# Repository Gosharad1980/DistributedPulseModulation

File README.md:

# DistributedPulseModulation

Distributed pulse modulation done like with the old P82C150, but with descrete components

## Theory of operation

With a regular Pulse Width Modulation (PWM), all the pulses are grouped in a same and unique pulse over the whole period.
On Distributed Pulse Modulation (DPM) and Dyadic Descrete Pulse Modulation (DDPM), the aim is to distribute all the "sub-pulses" throughout the whole period.

## Two advantages :
* spectrum with more high frequencies than PWM : easier filtering in case of A/D conversion
* as the pulse distribution is continuously evaluated : a threshold modification, before the period end, is taken into account without delay

### Old P82C150 for DPM implementation
[P82C150 - Application note](https://www.nxp.com/docs/en/application-note/AN94088.pdf)

[P82C150 datasheet](https://www.digchip.com/datasheets/parts/datasheet/364/P82C150AHT-pdf.php)

### DDPM implementation based on Paolo S. Crovetti thesis
[Thèse : Paolo S. Crovetti](https://www.researchgate.net/publication/309012492_All-Digital_High_Resolution_DA_Conversion_by_Dyadic_Digital_Pulse_Modulation)

## The breakout board

###  Features
	PWM (Pulse Width Modulation)
	DPM P82C150-like (Distributed Pulse Modulation)
	DDPM (Dyadic Discrete Pulse Modulation)

### MCP23017 Port A & B

	MCP23017 is an I2C 16bits IO expander
	Port A & B are used to control the board
	Prescaler decoding values :
	0x00	1
	0x01	2
	0x02	8
	0x03	16
	0x04	64
	0x05	256
	0x06	1024
	0x07	4096

## Choose your feature and do not populate the useless chips

### PWM

* do not populate the CD74HCT4053
* place the jumpers as describe in the silkscreen schematic (PWM)

### DPM

* do not populate the CD74HCT4053
* place the jumpers as describe in the silkscreen schematic (DPM/DDPM)

### DDPM

* do not populate the 74LS85
* place the jumpers as describe in the silkscreen schematic (DPM/DDPM)

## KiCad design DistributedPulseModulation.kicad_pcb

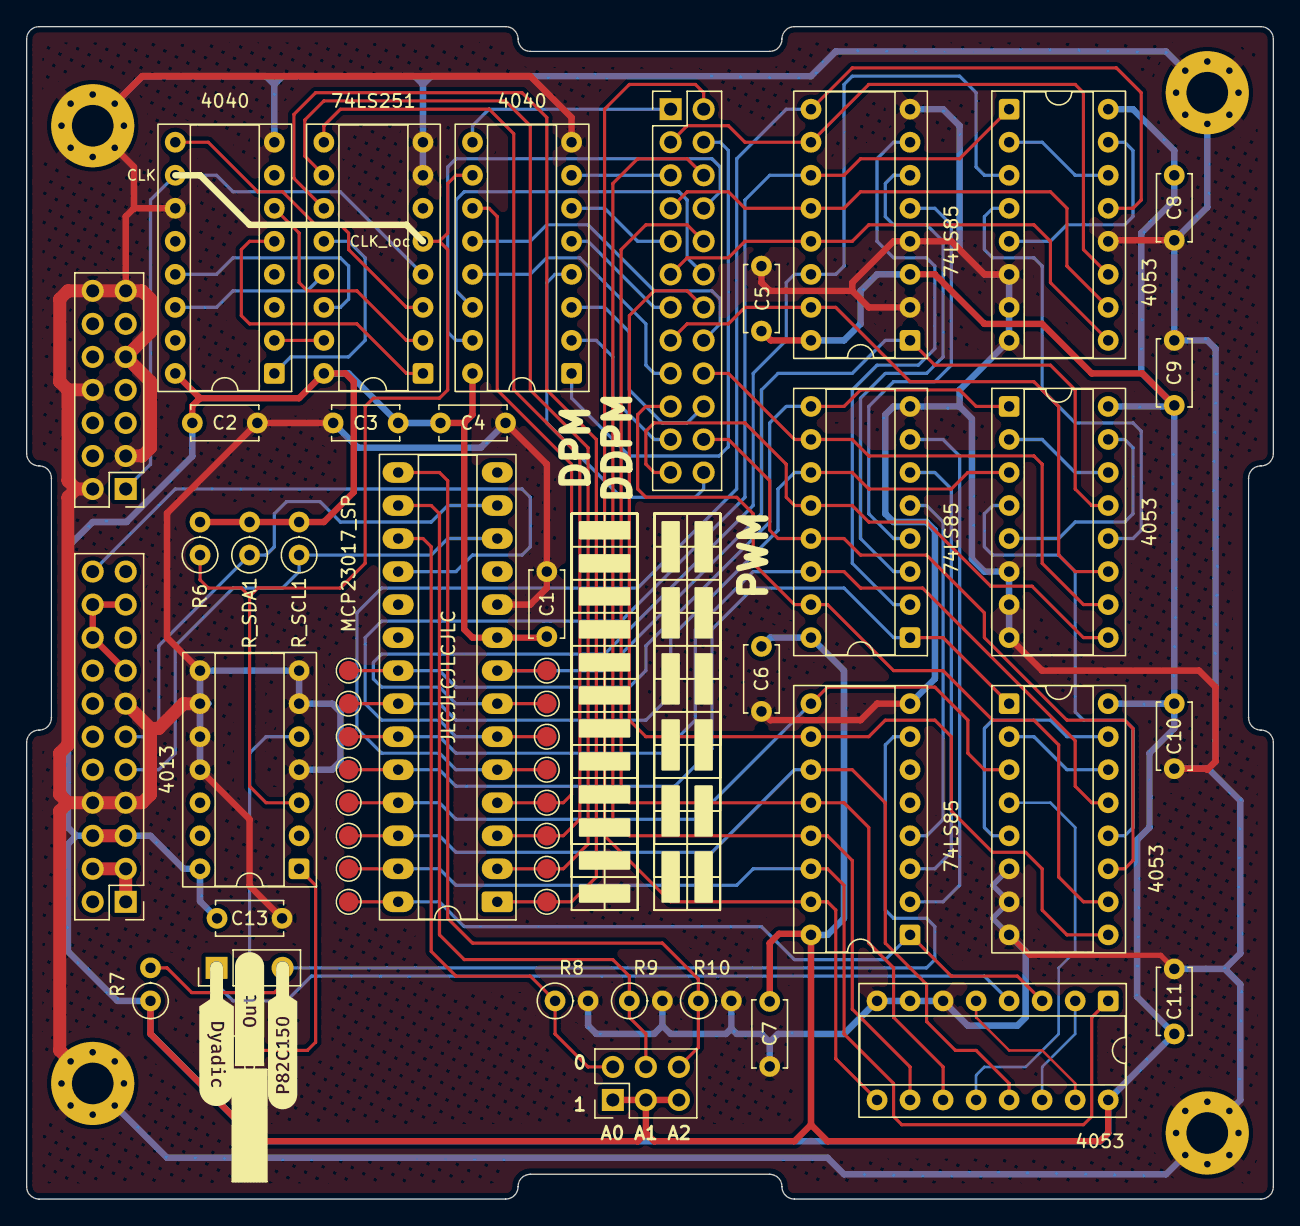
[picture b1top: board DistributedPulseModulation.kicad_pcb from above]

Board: 2 copper layers, 95.9 x 90.2 mm, 61 parts (1 on the bottom side), 80 nets.

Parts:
C1, C2, C3, C4, C5, C6, C7, C8, C9, C10, C11, C13: 0.1µF; C_Disc_D5.0mm_W2.5mm_P5.00mm
H1, H2, H3, H4: MountingHole_Pad; MountingHole_3.2mm_M3_Pad_Via
J1: Conn_02x12_Odd_Even; PinHeader_2x12_P2.54mm_Vertical
J2: Conn_01x01; PinSocket_1x01_P2.54mm_Horizontal
J3: Conn_02x03_Odd_Even; PinHeader_2x03_P2.54mm_Vertical
JP5: Jumper_3_Open; PinHeader_1x03_P2.54mm_Vertical
PCIe_CAN_1: Conn_02x07_Odd_Even; PinHeader_2x07_P2.54mm_Vertical
PCIe_SPI_1: Conn_02x11_Odd_Even; PinHeader_2x11_P2.54mm_Vertical
R6, R7, R8, R9, R10: 2.2K; R_Axial_DIN0207_L6.3mm_D2.5mm_P2.54mm_Vertical
R_SCL1: 4.7 kOhm; R_Axial_DIN0207_L6.3mm_D2.5mm_P2.54mm_Vertical
R_SDA1: 4.7 kOhm; R_Axial_DIN0207_L6.3mm_D2.5mm_P2.54mm_Vertical
TP_A0, TP_A1, TP_A2, TP_A3, TP_A4, TP_A5, TP_A6, TP_A7, TP_A8, TP_A9, TP_A10, TP_A11: TestPoint_Probe; TestPoint_Pad_D1.5mm
TP_PS0, TP_PS1, TP_PS2: TestPoint_Probe; TestPoint_Pad_D1.5mm
TP_~{CntEN}0: TestPoint_Probe; TestPoint_Pad_D1.5mm
U1: 74LS251; DIP-16_W7.62mm_Socket
U2: 4013; DIP-14_W7.62mm_Socket
U4: MCP23017_SP; DIP-28_W7.62mm_Socket_LongPads
U7, U10, U11, U12: 4053; DIP-16_W7.62mm_Socket
U8, U9: 4040; DIP-16_W7.62mm_Socket
U25, U28, U31: 74LS85; DIP-16_W7.62mm_Socket
kibuzzard-6ADD3B59: G***; kibuzzard-6ADD3B59
kibuzzard-68110D32: G***; kibuzzard-68110D32
kibuzzard-6811091F: G***; kibuzzard-6811091F
kibuzzard-68110930: G***; kibuzzard-68110930

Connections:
+5V: C1.2, C2.2, C3.2, C4.2, C5.2, C6.2, C7.2, C8.2, C9.2, C10.2, C11.2, C13.2, J3.1, J3.3, J3.5, PCIe_SPI_1.5, PCIe_SPI_1.6, R6.2, R7.1, R_SCL1.2, R_SDA1.2, U1.16 (VCC), U2.14 (VDD), U4.9 (VDD), U7.16 (VDD), U8.16 (VDD), U9.16 (VDD), U10.16 (VDD), U11.16 (VDD), U12.16 (VDD), U25.3 (Ia=b), U25.16 (VCC), U28.16 (VCC), U31.16 (VCC)
/A0: TP_A0.1 (1_1), U4.5 (GPB4), U7.13 (X1), U25.9 (B0)
/A1: TP_A1.1 (1_1), U4.6 (GPB5), U7.1 (Y1), U25.11 (B1)
/A2: TP_A2.1 (1_1), U4.7 (GPB6), U7.3 (Z1), U25.14 (B2)
/A3: TP_A3.1 (1_1), U4.8 (GPB7), U10.13 (X1), U25.1 (B3)
/A4: TP_A4.1 (1_1), U4.21 (GPA0), U10.1 (Y1), U28.9 (B0)
/A5: TP_A5.1 (1_1), U4.22 (GPA1), U10.3 (Z1), U28.11 (B1)
/A6: TP_A6.1 (1_1), U4.23 (GPA2), U11.13 (X1), U28.14 (B2)
/A7: TP_A7.1 (1_1), U4.24 (GPA3), U11.1 (Y1), U28.1 (B3)
/A8: TP_A8.1 (1_1), U4.25 (GPA4), U11.3 (Z1), U31.9 (B0)
/A9: TP_A9.1 (1_1), U4.26 (GPA5), U12.13 (X1), U31.11 (B1)
/A10: TP_A10.1 (1_1), U4.27 (GPA6), U12.1 (Y1), U31.14 (B2)
/A11: TP_A11.1 (1_1), U4.28 (GPA7), U12.3 (Z1), U31.1 (B3)
/ADR0: J3.2, R8.1, U4.17 (A2)
/ADR1: J3.4, R9.1, U4.16 (A1)
/ADR2: J3.6, R10.1, U4.15 (A0)
/Bus de fond panier/+3.3V: PCIe_SPI_1.15, PCIe_SPI_1.18, PCIe_SPI_1.19, PCIe_SPI_1.20
/Bus de fond panier/+Batt: PCIe_SPI_1.1, PCIe_SPI_1.3, PCIe_SPI_1.4
/CNT_A0: J1.2, U12.9 (C), U31.15 (A3)
/CNT_A1: J1.6, U12.10 (B), U31.13 (A2)
/CNT_A2: J1.10, U12.11 (A), U31.12 (A1)
/CNT_A3: J1.14, U11.9 (C), U31.10 (A0)
/CNT_A4: J1.19, U11.10 (B), U28.15 (A3)
/CNT_A5: J1.22, U11.11 (A), U28.13 (A2)
/CNT_A6: J1.23, U10.9 (C), U28.12 (A1)
/CNT_A7: J1.18, U10.10 (B), U28.10 (A0)
/CNT_A8: J1.15, U10.11 (A), U25.15 (A3)
/CNT_A9: J1.11, U7.9 (C), U25.13 (A2)
/CNT_A10: J1.7, U7.10 (B), U25.12 (A1)
/CNT_A11: J1.3, U7.11 (A), U25.10 (A0)
/Clock_loc: R6.1, U1.5 (Y), U2.3 (C), U8.10 (CLK)
/Div_2: U1.3 (I1), U9.9 (Q0)
/Div_8: U1.2 (I2), U9.6 (Q2)
/Div_16: U1.1 (I3), U9.5 (Q3)
/Div_64: U1.15 (I4), U9.2 (Q5)
/Div_256: U1.14 (I5), U9.13 (Q7)
/Div_1024: U1.13 (I6), U9.14 (Q9)
/Div_4096: U1.12 (I7), U9.1 (Q11)
/Q0: J1.1, U8.9 (Q0)
/Q1: J1.5, U8.7 (Q1)
/Q2: J1.9, U8.6 (Q2)
/Q3: J1.13, U8.5 (Q3)
/Q4: J1.20, U8.3 (Q4)
/Q5: J1.21, U8.2 (Q5)
/Q6: J1.24, U8.4 (Q6)
/Q7: J1.17, U8.13 (Q7)
/Q8: J1.16, U8.12 (Q8)
/Q9: J1.12, U8.14 (Q9)
/Q10: J1.8, U8.15 (Q10)
/Q11: J1.4, U8.1 (Q11)
Clock: PCIe_CAN_1.1, U1.4 (I0), U9.10 (CLK)
DDPM: JP5.1 (A), U12.4 (Z)
DPM: J2.1 (Pin_1_1), U2.1 (Q)
DPM_PWM: JP5.3 (B), R7.2, U31.7 (Oa<b)
Ground: C1.1, C2.1, C3.1, C4.1, C5.1, C6.1, C7.1, C8.1, C9.1, C10.1, C11.1, C13.1, H1.1 (1_1), H2.1 (1_1), H3.1 (1_1), H4.1 (1_1), PCIe_CAN_1.2, PCIe_CAN_1.3, PCIe_CAN_1.8, PCIe_CAN_1.9, PCIe_CAN_1.13, PCIe_CAN_1.14, PCIe_SPI_1.7, PCIe_SPI_1.8, PCIe_SPI_1.13, R8.2, R9.2, R10.2, U1.7 (~OE), U1.8 (GND), U2.4 (R), U2.6 (S), U2.7 (VSS), U2.8 (S), U2.9 (D), U2.10 (R), U2.11 (C), U4.10 (VSS), U7.6 (Inh), U7.7 (VEE), U7.8 (VSS), U7.12 (X0), U8.8 (VSS), U9.8 (VSS), U9.11 (Reset), U10.6 (Inh), U10.7 (VEE), U10.8 (VSS), U11.6 (Inh), U11.7 (VEE), U11.8 (VSS), U12.6 (Inh), U12.7 (VEE), U12.8 (VSS), U25.2 (Ia<b), U25.4 (Ia>b), U25.8 (GND), U28.8 (GND), U31.8 (GND)
unnamed: JP5.2 (C), U2.5 (D)
unnamed: U7.2 (Y0), U7.14 (X)
unnamed: U7.5 (Z0), U7.15 (Y)
unnamed: U7.4 (Z), U10.12 (X0)
unnamed: U10.2 (Y0), U10.14 (X)
unnamed: U10.5 (Z0), U10.15 (Y)
unnamed: U10.4 (Z), U11.12 (X0)
unnamed: U11.2 (Y0), U11.14 (X)
unnamed: U11.5 (Z0), U11.15 (Y)
unnamed: U11.4 (Z), U12.12 (X0)
unnamed: U12.2 (Y0), U12.14 (X)
unnamed: U12.5 (Z0), U12.15 (Y)
unnamed: U25.7 (Oa<b), U28.2 (Ia<b)
unnamed: U25.6 (Oa=b), U28.3 (Ia=b)
unnamed: U25.5 (Oa>b), U28.4 (Ia>b)
unnamed: U28.7 (Oa<b), U31.2 (Ia<b)
unnamed: U28.6 (Oa=b), U31.3 (Ia=b)
unnamed: U28.5 (Oa>b), U31.4 (Ia>b)
PreScaler0: TP_PS0.1 (1_1), U1.11 (S0), U4.1 (GPB0)
PreScaler1: TP_PS1.1 (1_1), U1.10 (S1), U4.2 (GPB1)
PreScaler2: TP_PS2.1 (1_1), U1.9 (S2), U4.3 (GPB2)
SCL: PCIe_SPI_1.9, R_SCL1.1, U4.12 (SCK)
SDA: PCIe_SPI_1.11, R_SDA1.1, U4.13 (SDA)
~CntEN: TP_~{CntEN}0.1 (1_1), U4.4 (GPB3), U8.11 (Reset)
~Reset: PCIe_SPI_1.22, U4.18 (~RESET)

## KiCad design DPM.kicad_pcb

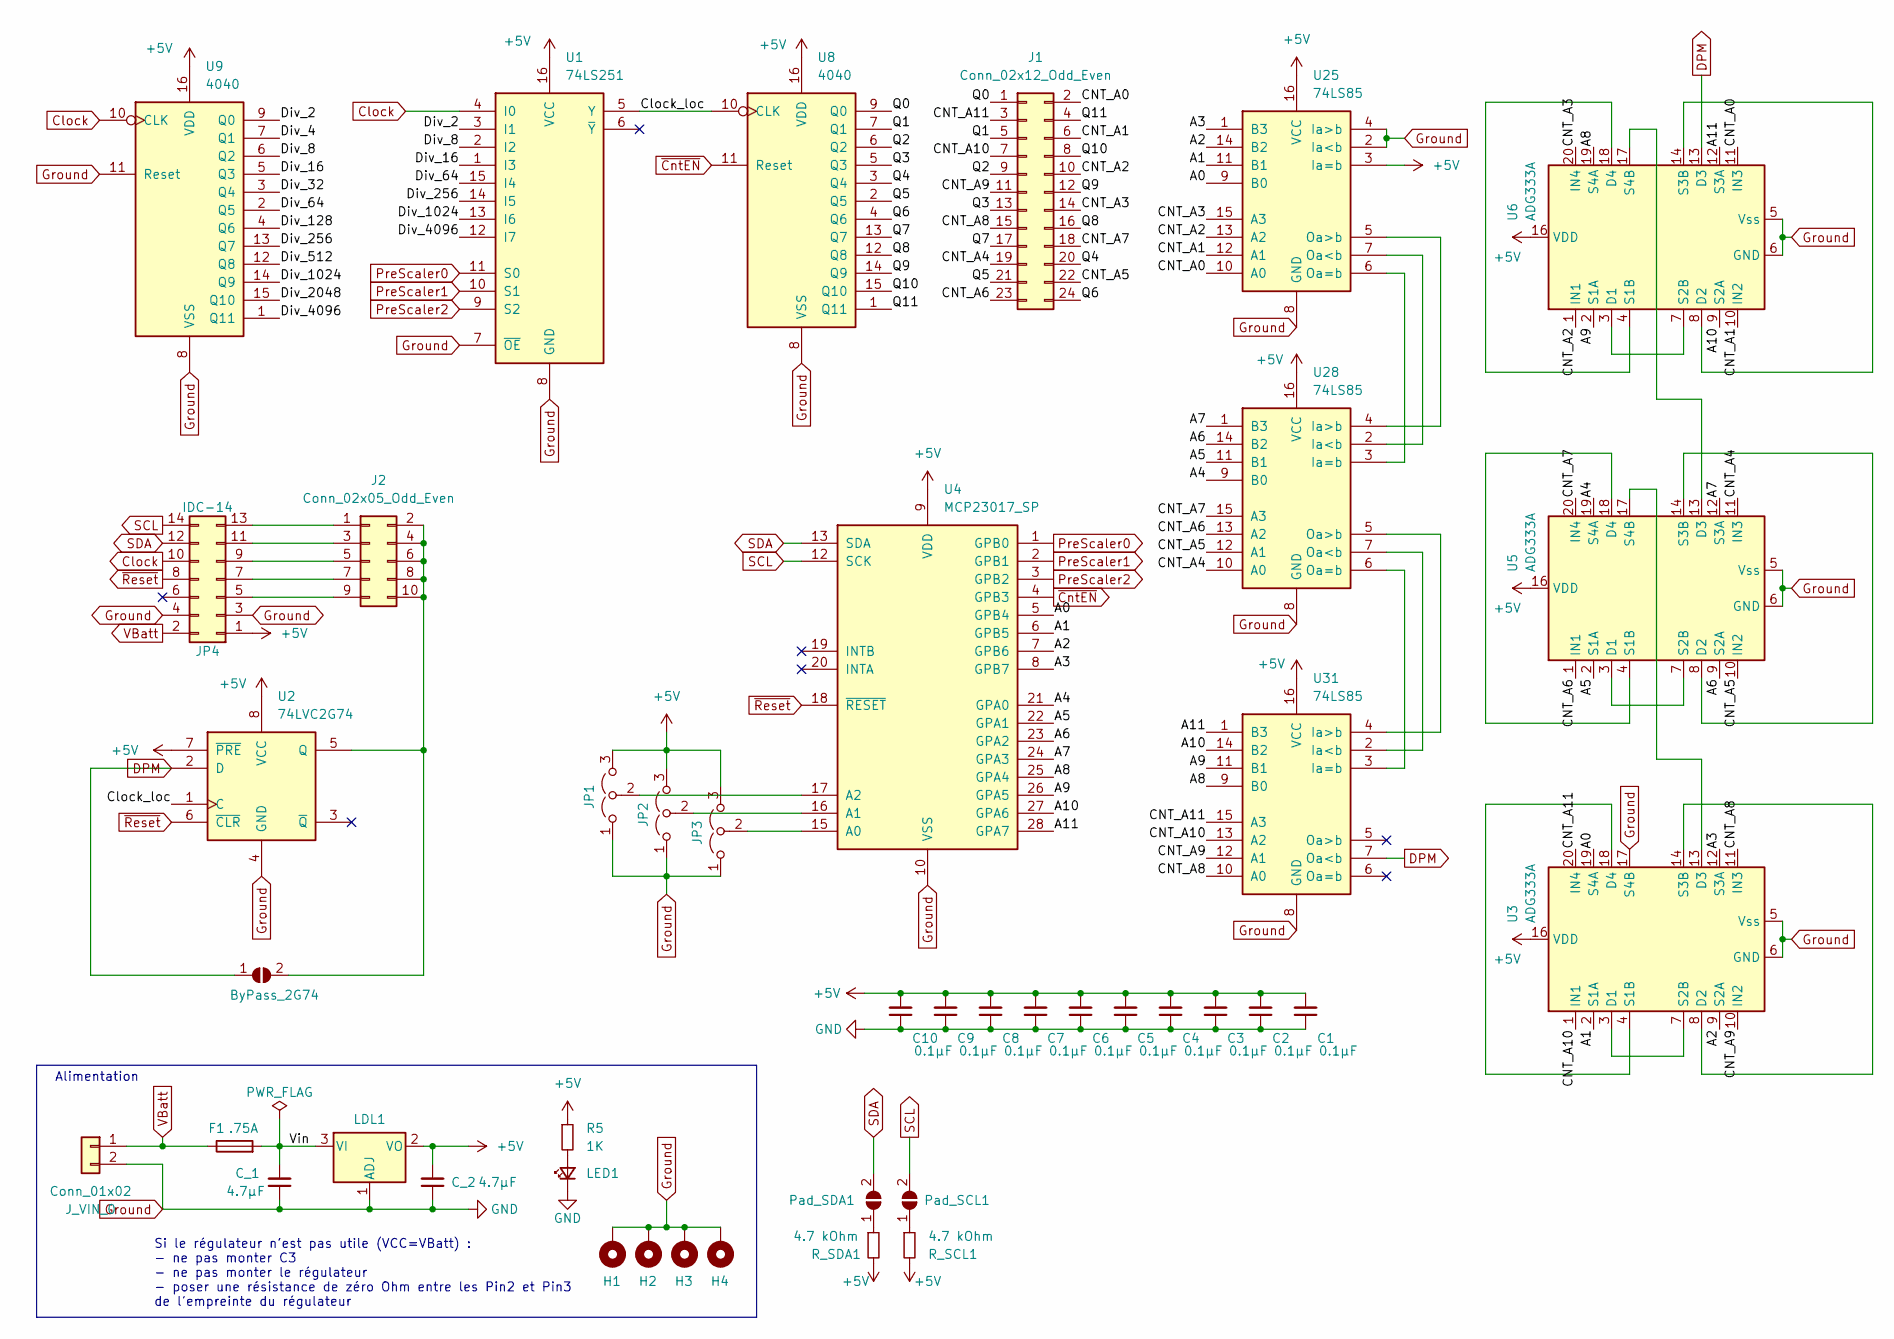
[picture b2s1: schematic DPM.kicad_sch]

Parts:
ByPass_2G74: SolderJumper_2_Open; SolderJumper-2_P1.3mm_Open_TrianglePad1.0x1.5mm
C1, C2, C3, C4, C5, C6, C7, C8, C9, C10: 0.1µF; C_Disc_D5.0mm_W2.5mm_P5.00mm
C_1, C_2: 4.7µF; C_1206_3216Metric_Pad1.33x1.80mm_HandSolder
F1: .75A; Fuse_1206_3216Metric_Pad1.42x1.75mm_HandSolder
H1, H2, H3, H4: MountingHole_Pad; MountingHole_3.2mm_M3_Pad_Via
J1: Conn_02x12_Odd_Even; PinHeader_2x12_P2.54mm_Vertical
J2: Conn_02x05_Odd_Even; PinHeader_2x05_P2.54mm_Vertical
JP1, JP2, JP3: Jumper_3_Open; PinHeader_1x03_P2.54mm_Vertical
JP4: IDC-14; IDC-Header_2x07_P2.54mm_Horizontal
J_VIN_0: Conn_01x02; PinHeader_1x02_P2.54mm_Vertical
LDL1: LDL1117; SOT-223-3_TabPin2
LED1: LED; LED_1206_3216Metric_Pad1.42x1.75mm_HandSolder
Pad_SCL1: SolderJumper_2_Open; SolderJumper-2_P1.3mm_Open_TrianglePad1.0x1.5mm
Pad_SDA1: SolderJumper_2_Open; SolderJumper-2_P1.3mm_Open_TrianglePad1.0x1.5mm
R5: 1K; R_1206_3216Metric_Pad1.30x1.75mm_HandSolder
R_SCL1: 4.7 kOhm; R_1210_3225Metric_Pad1.30x2.65mm_HandSolder
R_SDA1: 4.7 kOhm; R_1210_3225Metric_Pad1.30x2.65mm_HandSolder
U1: 74LS251; DIP-16_W7.62mm_Socket
U2: 74LVC2G74; SSOP-8_2.95x2.8mm_P0.65mm
U3, U5, U6: ADG333A; DIP-20_W7.62mm_Socket_LongPads
U4: MCP23017_SP; DIP-28_W7.62mm_Socket_LongPads
U8, U9: 4040; DIP-16_W7.62mm_Socket
U25, U28, U31: 74LS85; DIP-16_W7.62mm_Socket

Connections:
+5V: C1.2, C2.2, C3.2, C4.2, C5.2, C6.2, C7.2, C8.2, C9.2, C10.2, C_2.2, JP1.3 (B), JP2.3 (B), JP3.3 (B), JP4.1, LDL1.2 (VO), R5.1, R_SCL1.2, R_SDA1.2, U1.16 (VCC), U2.7 (~PRE), U2.8 (VCC), U3.16 (VDD), U4.9 (VDD), U5.16 (VDD), U6.16 (VDD), U8.16 (VDD), U9.16 (VDD), U25.3 (Ia=b), U25.16 (VCC), U28.16 (VCC), U31.16 (VCC)
/A0: U3.19 (S4A), U4.5 (GPB4), U25.9 (B0)
/A1: U3.2 (S1A), U4.6 (GPB5), U25.11 (B1)
/A2: U3.9 (S2A), U4.7 (GPB6), U25.14 (B2)
/A3: U3.12 (S3A), U4.8 (GPB7), U25.1 (B3)
/A4: U4.21 (GPA0), U5.19 (S4A), U28.9 (B0)
/A5: U4.22 (GPA1), U5.2 (S1A), U28.11 (B1)
/A6: U4.23 (GPA2), U5.9 (S2A), U28.14 (B2)
/A7: U4.24 (GPA3), U5.12 (S3A), U28.1 (B3)
/A8: U4.25 (GPA4), U6.19 (S4A), U31.9 (B0)
/A9: U4.26 (GPA5), U6.2 (S1A), U31.11 (B1)
/A10: U4.27 (GPA6), U6.9 (S2A), U31.14 (B2)
/A11: U4.28 (GPA7), U6.12 (S3A), U31.1 (B3)
/CNT_A0: J1.2, U6.11 (IN3), U25.10 (A0)
/CNT_A1: J1.6, U6.10 (IN2), U25.12 (A1)
/CNT_A2: J1.10, U6.1 (IN1), U25.13 (A2)
/CNT_A3: J1.14, U6.20 (IN4), U25.15 (A3)
/CNT_A4: J1.19, U5.11 (IN3), U28.10 (A0)
/CNT_A5: J1.22, U5.10 (IN2), U28.12 (A1)
/CNT_A6: J1.23, U5.1 (IN1), U28.13 (A2)
/CNT_A7: J1.18, U5.20 (IN4), U28.15 (A3)
/CNT_A8: J1.15, U3.11 (IN3), U31.10 (A0)
/CNT_A9: J1.11, U3.10 (IN2), U31.12 (A1)
/CNT_A10: J1.7, U3.1 (IN1), U31.13 (A2)
/CNT_A11: J1.3, U3.20 (IN4), U31.15 (A3)
/Clock_loc: U1.5 (Y), U2.1 (C), U8.10 (CLK)
/Div_2: U1.3 (I1), U9.9 (Q0)
/Div_4: U9.7 (Q1)
/Div_8: U1.2 (I2), U9.6 (Q2)
/Div_16: U1.1 (I3), U9.5 (Q3)
/Div_32: U9.3 (Q4)
/Div_64: U1.15 (I4), U9.2 (Q5)
/Div_128: U9.4 (Q6)
/Div_256: U1.14 (I5), U9.13 (Q7)
/Div_512: U9.12 (Q8)
/Div_1024: U1.13 (I6), U9.14 (Q9)
/Div_2048: U9.15 (Q10)
/Div_4096: U1.12 (I7), U9.1 (Q11)
/Q0: J1.1, U8.9 (Q0)
/Q1: J1.5, U8.7 (Q1)
/Q2: J1.9, U8.6 (Q2)
/Q3: J1.13, U8.5 (Q3)
/Q4: J1.20, U8.3 (Q4)
/Q5: J1.21, U8.2 (Q5)
/Q6: J1.24, U8.4 (Q6)
/Q7: J1.17, U8.13 (Q7)
/Q8: J1.16, U8.12 (Q8)
/Q9: J1.12, U8.14 (Q9)
/Q10: J1.8, U8.15 (Q10)
/Q11: J1.4, U8.1 (Q11)
/Vin: C_1.2, F1.2, LDL1.3 (VI)
Clock: JP4.10, U1.4 (I0), U9.10 (CLK)
DPM: ByPass_2G74.1 (A), U2.2 (D), U6.13 (D3), U31.7 (Oa<b)
Ground: C1.1, C2.1, C3.1, C4.1, C5.1, C6.1, C7.1, C8.1, C9.1, C10.1, C_1.1, C_2.1, H1.1, H2.1, H3.1, H4.1, JP1.1 (A), JP2.1 (A), JP3.1 (A), JP4.3, JP4.4, J_VIN_0.2, LDL1.1 (ADJ), LED1.1 (K), U1.7 (~OE), U1.8 (GND), U2.4 (GND), U3.5 (Vss), U3.6 (GND), U3.15 (NC), U3.17 (S4B), U4.10 (VSS), U5.5 (Vss), U5.6 (GND), U5.15 (NC), U6.5 (Vss), U6.6 (GND), U6.15 (NC), U8.8 (VSS), U9.8 (VSS), U9.11 (Reset), U25.2 (Ia<b), U25.4 (Ia>b), U25.8 (GND), U28.8 (GND), U31.8 (GND)
unnamed: ByPass_2G74.2 (B), J2.2, J2.4, J2.6, J2.8, J2.10, U2.5 (Q)
unnamed: J2.1, JP4.13
unnamed: J2.3, JP4.11
unnamed: J2.5, JP4.9
unnamed: J2.7, JP4.7
unnamed: J2.9, JP4.5
unnamed: JP1.2 (C), U4.17 (A2)
unnamed: JP2.2 (C), U4.16 (A1)
unnamed: JP3.2 (C), U4.15 (A0)
unnamed: LED1.2 (A), R5.2
unnamed: Pad_SCL1.1 (A), R_SCL1.1
unnamed: Pad_SDA1.1 (A), R_SDA1.1
unnamed: U3.3 (D1), U3.7 (S2B)
unnamed: U3.8 (D2), U3.14 (S3B)
unnamed: U3.13 (D3), U5.17 (S4B)
unnamed: U3.4 (S1B), U3.18 (D4)
unnamed: U5.3 (D1), U5.7 (S2B)
unnamed: U5.8 (D2), U5.14 (S3B)
unnamed: U5.13 (D3), U6.17 (S4B)
unnamed: U5.4 (S1B), U5.18 (D4)
unnamed: U6.3 (D1), U6.7 (S2B)
unnamed: U6.8 (D2), U6.14 (S3B)
unnamed: U6.4 (S1B), U6.18 (D4)
unnamed: U25.7 (Oa<b), U28.2 (Ia<b)
unnamed: U25.6 (Oa=b), U28.3 (Ia=b)
unnamed: U25.5 (Oa>b), U28.4 (Ia>b)
unnamed: U28.7 (Oa<b), U31.2 (Ia<b)
unnamed: U28.6 (Oa=b), U31.3 (Ia=b)
unnamed: U28.5 (Oa>b), U31.4 (Ia>b)
PreScaler0: U1.11 (S0), U4.1 (GPB0)
PreScaler1: U1.10 (S1), U4.2 (GPB1)
PreScaler2: U1.9 (S2), U4.3 (GPB2)
SCL: JP4.14, Pad_SCL1.2 (B), U4.12 (SCK)
SDA: JP4.12, Pad_SDA1.2 (B), U4.13 (SDA)
VBatt: F1.1, JP4.2, J_VIN_0.1
~CntEN: U4.4 (GPB3), U8.11 (Reset)
~Reset: JP4.8, U2.6 (~CLR), U4.18 (~RESET)

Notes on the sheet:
Alimentation
Si le régulateur n'est pas utile (VCC=VBatt) : - ne pas monter C3 - ne pas monter le régulateur - poser une résistance de zéro Ohm entre les Pin2 et Pin3 de l'empreinte du régulateur

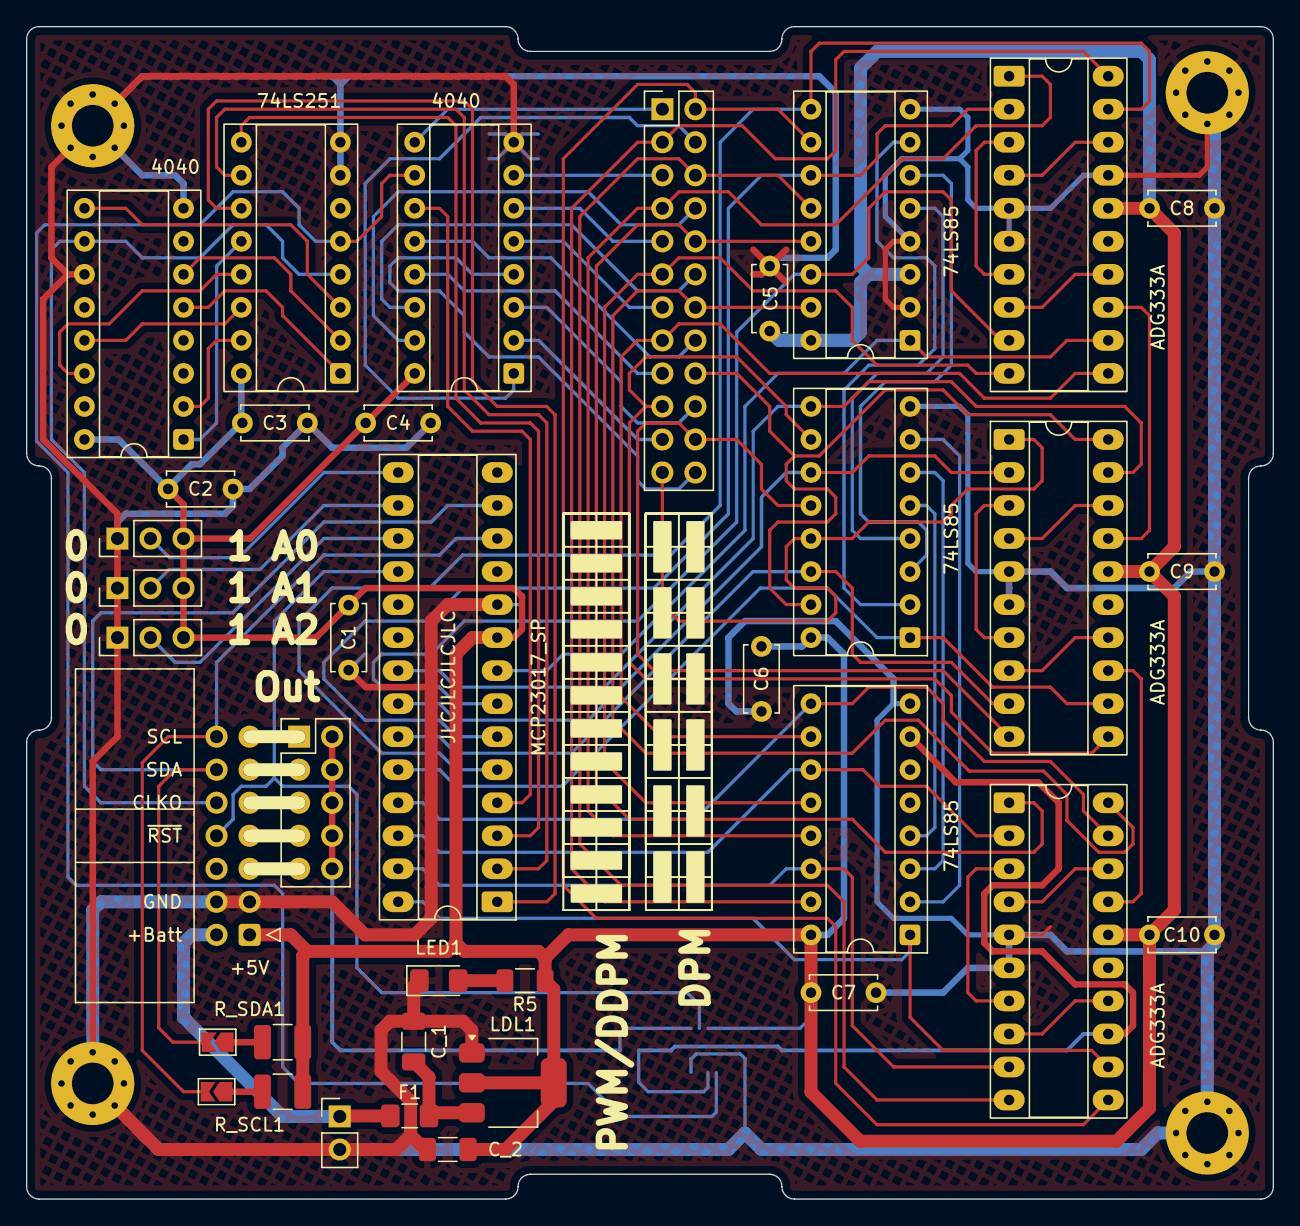
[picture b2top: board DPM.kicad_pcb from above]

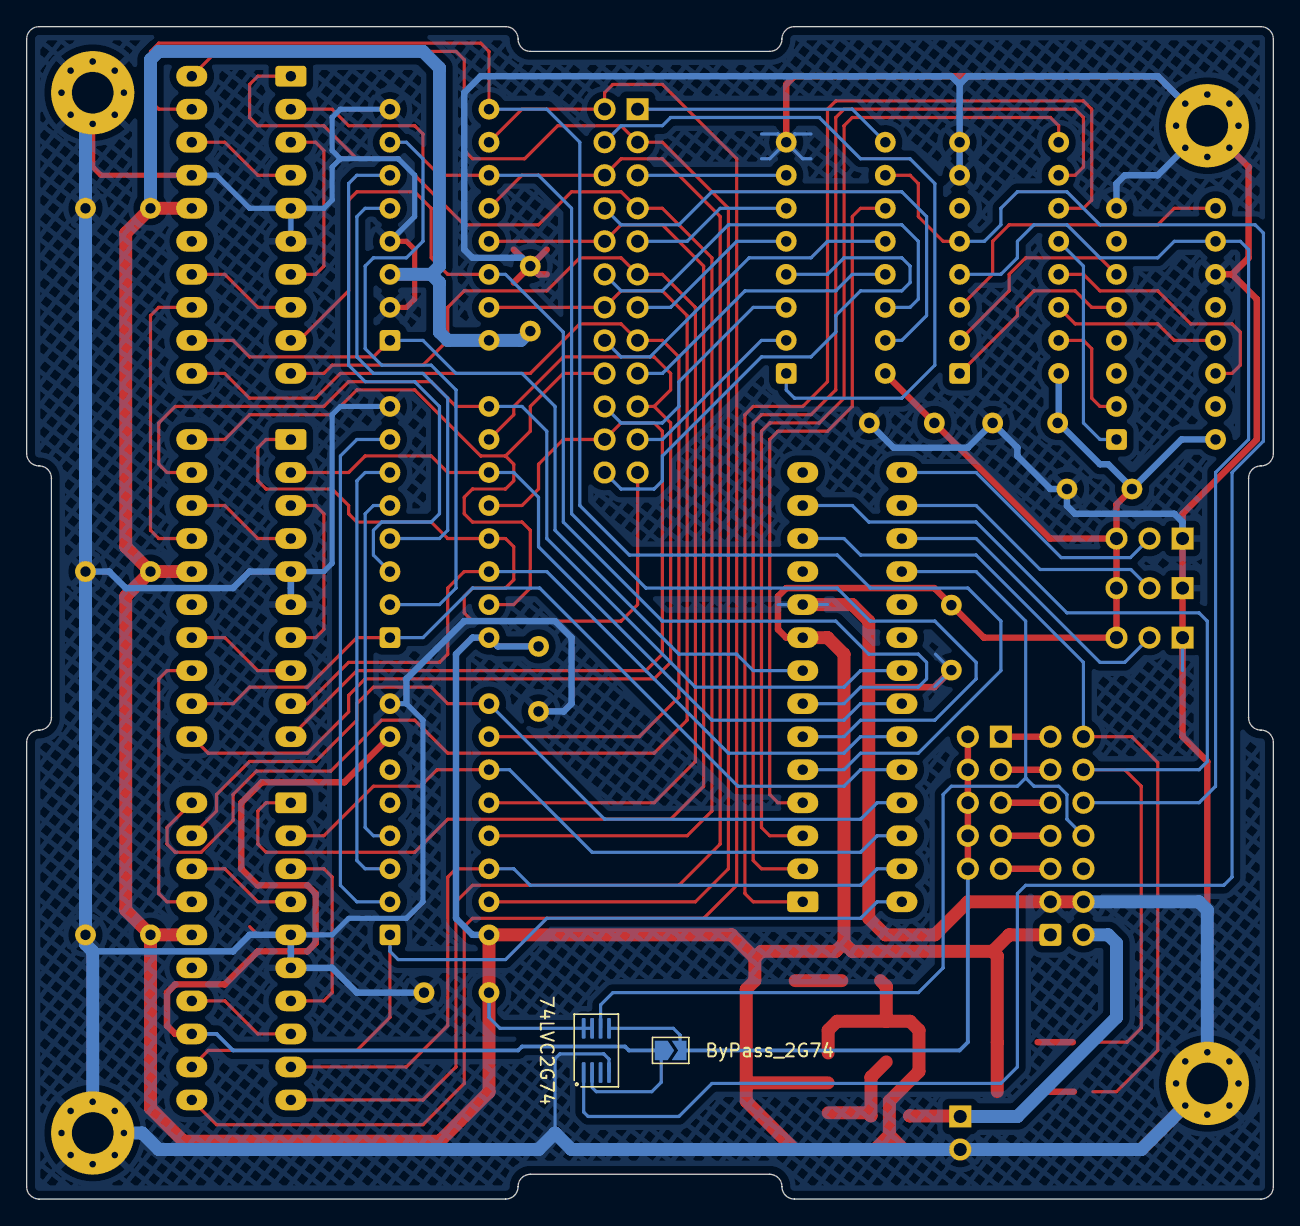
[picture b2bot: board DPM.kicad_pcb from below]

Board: 2 copper layers, 95.9 x 90.2 mm, 43 parts (2 on the bottom side), 86 nets.

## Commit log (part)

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2024-08-17 Imported folder structure
2024-08-17 On démarre un nouveau projet mort-né
2024-08-20 DPM et DDPM implémentés Mouais bof pour ajouter ma DPM en code Gray
    Sinon OK Tiers pour en faire la branche 1
2025-03-26 - Ajout de screenshots de doc
2025-03-28 + 3 fonctionnalités : PWM, DPM & DDPM + début du routage de la carte
2025-03-28 POPOPO !!!!! 1ere version du routage de la carte
2025-03-29 Ajout du prescaler TODO : - condensateurs de découplage - bouchon I2C
2025-03-29 Début de ré&vision pour ajouter des câblages
2025-03-29 Ajout pistes An sur DDPM Suppression du via des enfers Ajout jumpers pour DPM sur connecteur IDC-14 Début du silksreen
    TODO :
    - condensateurs de découplage
    - bouchon I2C
2025-03-29 Nouvelle liste de prescaler : 1 2 8 16 64 256 1024 4096
2025-03-30 - Condo UC - résintances pull-up I2C - D-latch 2G74 - routage - silkscreen
2025-03-30 Correction clock du 2G74 Reroutage léger
2025-03-30 Modification : PinOut des ports GPIOA et GPIOB
2025-03-31 Création modélisations sous Digital Correction routage des R SDA/SCL Ajout des screenshots de la carte
2025-03-31 Rename en DistributedPulseModulation.
2025-03-31 RENAME : suite et fin
2025-03-31 MOVE : déplacement de jpg dans le répertoire img
2025-03-31 Création du README.md Ajout de screenshot et de commentaires
2025-03-31 Correction README.md
2025-04-01 RETROFIT : connecteur perso PCIe_CAN pour compatibilité avec le CANduino128 comme microcontôleur maitre
2025-04-02 AMELIORATION : simplification des routages de pistes
2025-04-03 Fin de simplification du routage. Génération des Gerber.
2025-04-04 Full rework : ADG333A 10x plus chers que cd74hct4053 Nouveau chips et nouveau routage JPP TT
2025-04-04 Simplification du routage
2025-04-04 Enfin une version industrialisable et pas chers ? - correction du routage - replacement de condensateurs - génération des gerber
2025-04-04 Correction documentaire : README.md
2025-04-04 Completion README.md avec les liens web des docs P82C150 et la thèse en question.
2025-04-05 Modification fonctionnelle : - PWM en "mode croisé" des jumpers - DPM en "mode direct" des jumpers comme le DDPM
    Routage
2025-04-05 Utilisation de KiVar pour gérer les variantes du PCB :)
2025-04-06 Feature : - DPM et DDPM sur même position de jumper - PWM sur jumpers en croisés
    KiVar :
    - création des 4 aspects FULL, PWM, DPM et DDPM
    Doc/img :
    - mise à jour du README.md
    - mise à jour des screeshots
    - intégration directe dans le projet des modèles 3D
2025-04-06 Génération des gerber
2025-04-07 Ajout des fichiers JLCPCB à l'ignore list
2025-04-09 Traduction : README.md translated into english
2025-04-25 Correction position R_SDA, R_SCL, jumper A0, A1 et A2
2025-04-27 Travaux préparatoire : V2.0 - Ajout jumper Dyadic vs P82C150 - B.Silkscreen major update
    TODO :
    - Suppression connecteur IDC
    - Ajout pinheader horizontal pour les 5 outputs
2025-04-27 Pré-version de la v2.0
2025-04-27 Readme update + photos
2025-04-29 Reroutage et passage de tous les composants côté Front
2025-04-29 V2.0 : SCH + PCB + Gerber
2025-04-29 PCB_V2.0 delivery and README.md update
2025-05-02 doc pdf update
2025-05-08 Routage : légère modif de la route du GND
2025-05-08 RCA : 2.0->1.x - correction KiVar pour "mixer" - ajout /ClkEN au connecteur IDC14 - routage /ClkEN
2025-05-08 Ajout test-points pour les ports A et B du MCP23017 Léger reroutage
2025-05-10 Routage : Clock_loc on PIN6 of IDC-14
2025-05-17 readme update : adding prescaler decoding values
2025-07-13 Ajout licence CC-BY-SA-4.0
2025-10-28 update : gitignore
